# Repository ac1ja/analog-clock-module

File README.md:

# analog-clock-module

This repo contains all the firmware and hardware for the analog-clock-module.

If you're looking for the latest docs/builds, see our [Releases Page](https://github.com/ac1ja/analog-clock-module/releases).

# Getting Started

First, clone this repo (and optionally checkout a branch)

```shell
git clone https://github.com/ac1ja/analog-clock-module.git
cd analog-clock-module
```

# Init Submodules

Some libraries and resources are included as submodules, run the following
command to initialize them before opening the main sch

(If you get a missing library error, make sure to do this)

```shell
git submodule update --init --recursive
```

## Project Layout

If you want to use this project template for yourself, you can find it [here!](https://github.com/KenwoodFox/Project-Template)

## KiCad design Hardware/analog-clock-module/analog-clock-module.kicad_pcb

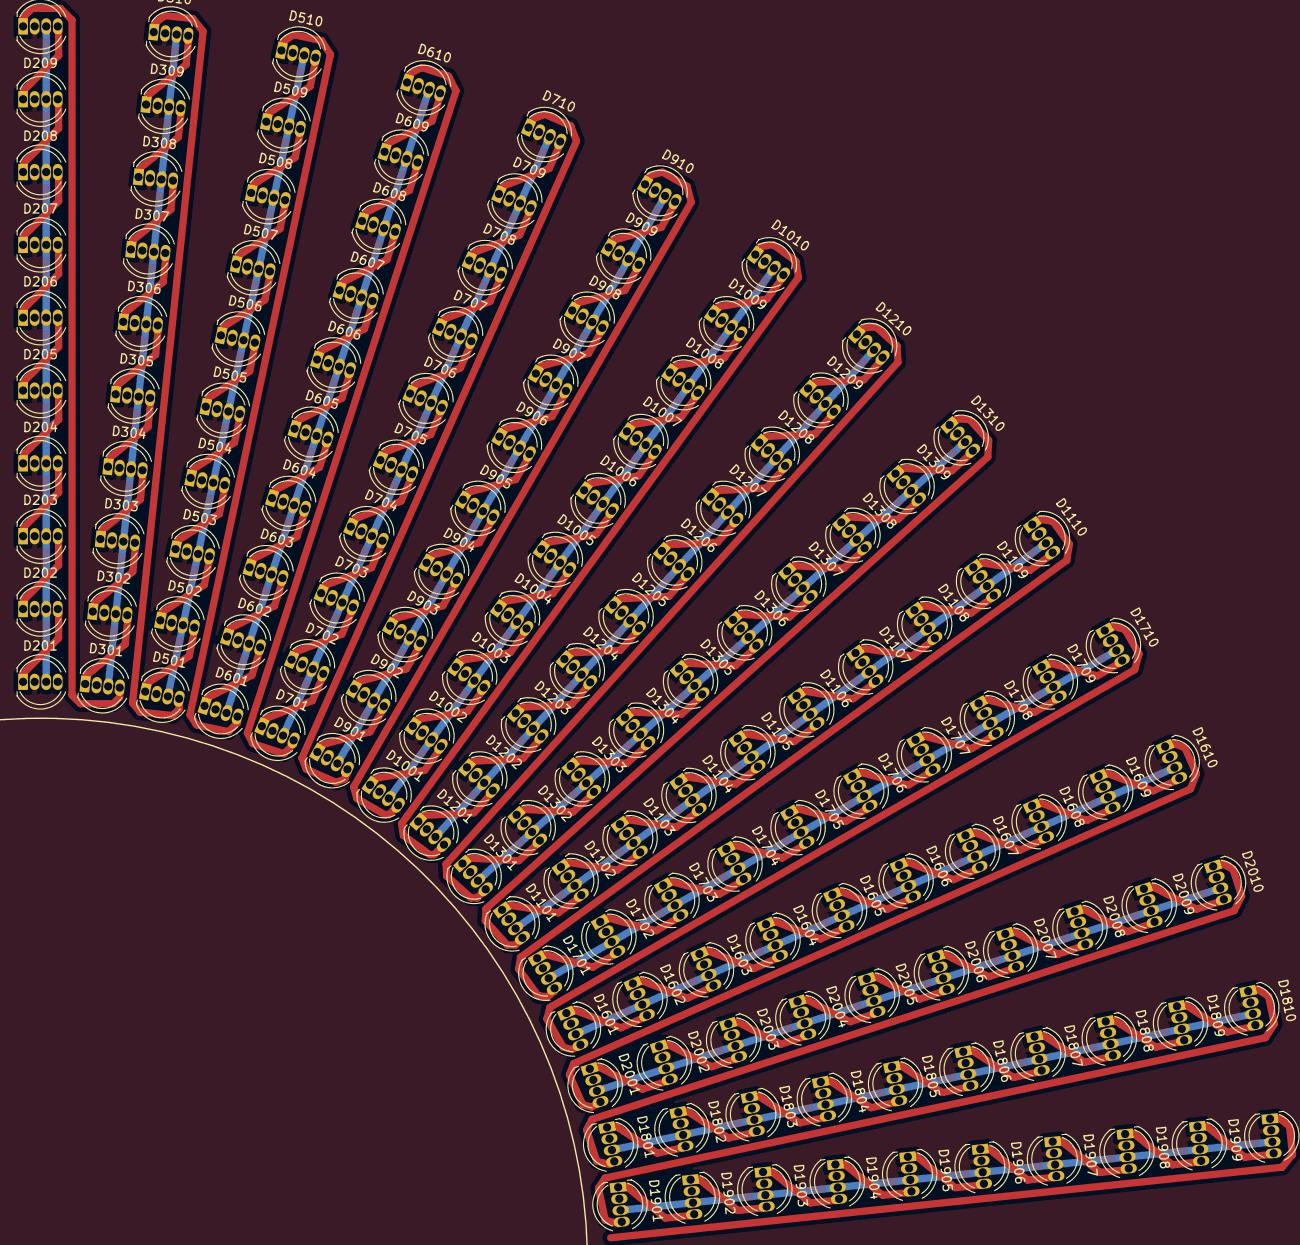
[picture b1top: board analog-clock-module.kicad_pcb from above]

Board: 2 copper layers, 150 parts (0 on the bottom side), 151 nets.

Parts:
D201, D202, D203, D204, D205, D206, D207, D208, D209, D210, D301, D302, D303, D304, D305, D306, D307, D308, D309, D310, D501, D502, D503, D504, D505, D506, D507, D508, D509, D510, D601, D602, D603, D604, D605, D606, D607, D608, D609, D610, D701, D702, D703, D704, D705, D706, D707, D708, D709, D710, D901, D902, D903, D904, D905, D906, D907, D908, D909, D910, D1001, D1002, D1003, D1004, D1005, D1006, D1007, D1008, D1009, D1010, D1101, D1102, D1103, D1104, D1105, D1106, D1107, D1108, D1109, D1110, D1201, D1202, D1203, D1204, D1205, D1206, D1207, D1208, D1209, D1210, D1301, D1302, D1303, D1304, D1305, D1306, D1307, D1308, D1309, D1310, D1601, D1602, D1603, D1604, D1605, D1606, D1607, D1608, D1609, D1610, D1701, D1702, D1703, D1704, D1705, D1706, D1707, D1708, D1709, D1710, D1801, D1802, D1803, D1804, D1805, D1806, D1807, D1808, D1809, D1810, D1901, D1902, D1903, D1904, D1905, D1906, D1907, D1908, D1909, D1910, D2001, D2002, D2003, D2004, D2005, D2006, D2007, D2008, D2009, D2010: NeoPixel_THT; LED_D5.0mm-4_RGB

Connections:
+5V: D201.3 (VDD), D202.3 (VDD), D203.3 (VDD), D204.3 (VDD), D205.3 (VDD), D206.3 (VDD), D207.3 (VDD), D208.3 (VDD), D209.3 (VDD), D210.3 (VDD), D301.3 (VDD), D302.3 (VDD), D303.3 (VDD), D304.3 (VDD), D305.3 (VDD), D306.3 (VDD), D307.3 (VDD), D308.3 (VDD), D309.3 (VDD), D310.3 (VDD), D501.3 (VDD), D502.3 (VDD), D503.3 (VDD), D504.3 (VDD), D505.3 (VDD), D506.3 (VDD), D507.3 (VDD), D508.3 (VDD), D509.3 (VDD), D510.3 (VDD), D601.3 (VDD), D602.3 (VDD), D603.3 (VDD), D604.3 (VDD), D605.3 (VDD), D606.3 (VDD), D607.3 (VDD), D608.3 (VDD), D609.3 (VDD), D610.3 (VDD), D701.3 (VDD), D702.3 (VDD), D703.3 (VDD), D704.3 (VDD), D705.3 (VDD), D706.3 (VDD), D707.3 (VDD), D708.3 (VDD), D709.3 (VDD), D710.3 (VDD), D901.3 (VDD), D902.3 (VDD), D903.3 (VDD), D904.3 (VDD), D905.3 (VDD), D906.3 (VDD), D907.3 (VDD), D908.3 (VDD), D909.3 (VDD), D910.3 (VDD), D1001.3 (VDD), D1002.3 (VDD), D1003.3 (VDD), D1004.3 (VDD), D1005.3 (VDD), D1006.3 (VDD), D1007.3 (VDD), D1008.3 (VDD), D1009.3 (VDD), D1010.3 (VDD), D1101.3 (VDD), D1102.3 (VDD), D1103.3 (VDD), D1104.3 (VDD), D1105.3 (VDD), D1106.3 (VDD), D1107.3 (VDD), D1108.3 (VDD), D1109.3 (VDD), D1110.3 (VDD), D1201.3 (VDD), D1202.3 (VDD), D1203.3 (VDD), D1204.3 (VDD), D1205.3 (VDD), D1206.3 (VDD), D1207.3 (VDD), D1208.3 (VDD), D1209.3 (VDD), D1210.3 (VDD), D1301.3 (VDD), D1302.3 (VDD), D1303.3 (VDD), D1304.3 (VDD), D1305.3 (VDD), D1306.3 (VDD), D1307.3 (VDD), D1308.3 (VDD), D1309.3 (VDD), D1310.3 (VDD), D1601.3 (VDD), D1602.3 (VDD), D1603.3 (VDD), D1604.3 (VDD), D1605.3 (VDD), D1606.3 (VDD), D1607.3 (VDD), D1608.3 (VDD), D1609.3 (VDD), D1610.3 (VDD), D1701.3 (VDD), D1702.3 (VDD), D1703.3 (VDD), D1704.3 (VDD), D1705.3 (VDD), D1706.3 (VDD), D1707.3 (VDD), D1708.3 (VDD), D1709.3 (VDD), D1710.3 (VDD), D1801.3 (VDD), D1802.3 (VDD), D1803.3 (VDD), D1804.3 (VDD), D1805.3 (VDD), D1806.3 (VDD), D1807.3 (VDD), D1808.3 (VDD), D1809.3 (VDD), D1810.3 (VDD), D1901.3 (VDD), D1902.3 (VDD), D1903.3 (VDD), D1904.3 (VDD), D1905.3 (VDD), D1906.3 (VDD), D1907.3 (VDD), D1908.3 (VDD), D1909.3 (VDD), D1910.3 (VDD), D2001.3 (VDD), D2002.3 (VDD), D2003.3 (VDD), D2004.3 (VDD), D2005.3 (VDD), D2006.3 (VDD), D2007.3 (VDD), D2008.3 (VDD), D2009.3 (VDD), D2010.3 (VDD)
/Quadrant/Hour1/Clock Inner Hand1/DOUT: D210.1 (DOUT), D301.4 (DIN)
/Quadrant/Hour1/Clock Inner Hand2/DOUT: D310.1 (DOUT), D501.4 (DIN)
/Quadrant/Hour1/Clock Inner Hand3/DOUT: D510.1 (DOUT), D601.4 (DIN)
/Quadrant/Hour1/Clock Inner Hand4/DOUT: D610.1 (DOUT), D701.4 (DIN)
/Quadrant/Hour1/DOUT: D710.1 (DOUT), D901.4 (DIN)
/Quadrant/Hour2/Clock Inner Hand1/DOUT: D910.1 (DOUT), D1001.4 (DIN)
/Quadrant/Hour2/Clock Inner Hand2/DOUT: D1010.1 (DOUT), D1201.4 (DIN)
/Quadrant/Hour2/Clock Inner Hand3/DOUT: D1210.1 (DOUT), D1301.4 (DIN)
/Quadrant/Hour2/Clock Inner Hand4/DOUT: D1101.4 (DIN), D1310.1 (DOUT)
/Quadrant/Hour2/DOUT: D1110.1 (DOUT), D1701.4 (DIN)
/Quadrant/Hour3/Clock Inner Hand1/DOUT: D1601.4 (DIN), D1710.1 (DOUT)
/Quadrant/Hour3/Clock Inner Hand2/DOUT: D1610.1 (DOUT), D2001.4 (DIN)
/Quadrant/Hour3/Clock Inner Hand3/DOUT: D1801.4 (DIN), D2010.1 (DOUT)
/Quadrant/Hour3/Clock Inner Hand4/DOUT: D1810.1 (DOUT), D1901.4 (DIN)
GND: D201.2 (GND), D202.2 (GND), D203.2 (GND), D204.2 (GND), D205.2 (GND), D206.2 (GND), D207.2 (GND), D208.2 (GND), D209.2 (GND), D210.2 (GND), D301.2 (GND), D302.2 (GND), D303.2 (GND), D304.2 (GND), D305.2 (GND), D306.2 (GND), D307.2 (GND), D308.2 (GND), D309.2 (GND), D310.2 (GND), D501.2 (GND), D502.2 (GND), D503.2 (GND), D504.2 (GND), D505.2 (GND), D506.2 (GND), D507.2 (GND), D508.2 (GND), D509.2 (GND), D510.2 (GND), D601.2 (GND), D602.2 (GND), D603.2 (GND), D604.2 (GND), D605.2 (GND), D606.2 (GND), D607.2 (GND), D608.2 (GND), D609.2 (GND), D610.2 (GND), D701.2 (GND), D702.2 (GND), D703.2 (GND), D704.2 (GND), D705.2 (GND), D706.2 (GND), D707.2 (GND), D708.2 (GND), D709.2 (GND), D710.2 (GND), D901.2 (GND), D902.2 (GND), D903.2 (GND), D904.2 (GND), D905.2 (GND), D906.2 (GND), D907.2 (GND), D908.2 (GND), D909.2 (GND), D910.2 (GND), D1001.2 (GND), D1002.2 (GND), D1003.2 (GND), D1004.2 (GND), D1005.2 (GND), D1006.2 (GND), D1007.2 (GND), D1008.2 (GND), D1009.2 (GND), D1010.2 (GND), D1101.2 (GND), D1102.2 (GND), D1103.2 (GND), D1104.2 (GND), D1105.2 (GND), D1106.2 (GND), D1107.2 (GND), D1108.2 (GND), D1109.2 (GND), D1110.2 (GND), D1201.2 (GND), D1202.2 (GND), D1203.2 (GND), D1204.2 (GND), D1205.2 (GND), D1206.2 (GND), D1207.2 (GND), D1208.2 (GND), D1209.2 (GND), D1210.2 (GND), D1301.2 (GND), D1302.2 (GND), D1303.2 (GND), D1304.2 (GND), D1305.2 (GND), D1306.2 (GND), D1307.2 (GND), D1308.2 (GND), D1309.2 (GND), D1310.2 (GND), D1601.2 (GND), D1602.2 (GND), D1603.2 (GND), D1604.2 (GND), D1605.2 (GND), D1606.2 (GND), D1607.2 (GND), D1608.2 (GND), D1609.2 (GND), D1610.2 (GND), D1701.2 (GND), D1702.2 (GND), D1703.2 (GND), D1704.2 (GND), D1705.2 (GND), D1706.2 (GND), D1707.2 (GND), D1708.2 (GND), D1709.2 (GND), D1710.2 (GND), D1801.2 (GND), D1802.2 (GND), D1803.2 (GND), D1804.2 (GND), D1805.2 (GND), D1806.2 (GND), D1807.2 (GND), D1808.2 (GND), D1809.2 (GND), D1810.2 (GND), D1901.2 (GND), D1902.2 (GND), D1903.2 (GND), D1904.2 (GND), D1905.2 (GND), D1906.2 (GND), D1907.2 (GND), D1908.2 (GND), D1909.2 (GND), D1910.2 (GND), D2001.2 (GND), D2002.2 (GND), D2003.2 (GND), D2004.2 (GND), D2005.2 (GND), D2006.2 (GND), D2007.2 (GND), D2008.2 (GND), D2009.2 (GND), D2010.2 (GND)
unnamed: D201.1 (DOUT), D202.4 (DIN)
unnamed: D202.1 (DOUT), D203.4 (DIN)
unnamed: D203.1 (DOUT), D204.4 (DIN)
unnamed: D204.1 (DOUT), D205.4 (DIN)
unnamed: D205.1 (DOUT), D206.4 (DIN)
unnamed: D206.1 (DOUT), D207.4 (DIN)
unnamed: D207.1 (DOUT), D208.4 (DIN)
unnamed: D208.1 (DOUT), D209.4 (DIN)
unnamed: D209.1 (DOUT), D210.4 (DIN)
unnamed: D301.1 (DOUT), D302.4 (DIN)
unnamed: D302.1 (DOUT), D303.4 (DIN)
unnamed: D303.1 (DOUT), D304.4 (DIN)
unnamed: D304.1 (DOUT), D305.4 (DIN)
unnamed: D305.1 (DOUT), D306.4 (DIN)
unnamed: D306.1 (DOUT), D307.4 (DIN)
unnamed: D307.1 (DOUT), D308.4 (DIN)
unnamed: D308.1 (DOUT), D309.4 (DIN)
unnamed: D309.1 (DOUT), D310.4 (DIN)
unnamed: D501.1 (DOUT), D502.4 (DIN)
unnamed: D502.1 (DOUT), D503.4 (DIN)
unnamed: D503.1 (DOUT), D504.4 (DIN)
unnamed: D504.1 (DOUT), D505.4 (DIN)
unnamed: D505.1 (DOUT), D506.4 (DIN)
unnamed: D506.1 (DOUT), D507.4 (DIN)
unnamed: D507.1 (DOUT), D508.4 (DIN)
unnamed: D508.1 (DOUT), D509.4 (DIN)
unnamed: D509.1 (DOUT), D510.4 (DIN)
unnamed: D601.1 (DOUT), D602.4 (DIN)
unnamed: D602.1 (DOUT), D603.4 (DIN)
unnamed: D603.1 (DOUT), D604.4 (DIN)
unnamed: D604.1 (DOUT), D605.4 (DIN)
unnamed: D605.1 (DOUT), D606.4 (DIN)
unnamed: D606.1 (DOUT), D607.4 (DIN)
unnamed: D607.1 (DOUT), D608.4 (DIN)
unnamed: D608.1 (DOUT), D609.4 (DIN)
unnamed: D609.1 (DOUT), D610.4 (DIN)
unnamed: D701.1 (DOUT), D702.4 (DIN)
unnamed: D702.1 (DOUT), D703.4 (DIN)
unnamed: D703.1 (DOUT), D704.4 (DIN)
unnamed: D704.1 (DOUT), D705.4 (DIN)
unnamed: D705.1 (DOUT), D706.4 (DIN)
unnamed: D706.1 (DOUT), D707.4 (DIN)
unnamed: D707.1 (DOUT), D708.4 (DIN)
unnamed: D708.1 (DOUT), D709.4 (DIN)
unnamed: D709.1 (DOUT), D710.4 (DIN)
unnamed: D901.1 (DOUT), D902.4 (DIN)
unnamed: D902.1 (DOUT), D903.4 (DIN)
unnamed: D903.1 (DOUT), D904.4 (DIN)
unnamed: D904.1 (DOUT), D905.4 (DIN)
unnamed: D905.1 (DOUT), D906.4 (DIN)
unnamed: D906.1 (DOUT), D907.4 (DIN)
unnamed: D907.1 (DOUT), D908.4 (DIN)
unnamed: D908.1 (DOUT), D909.4 (DIN)
unnamed: D909.1 (DOUT), D910.4 (DIN)
unnamed: D1001.1 (DOUT), D1002.4 (DIN)
unnamed: D1002.1 (DOUT), D1003.4 (DIN)
unnamed: D1003.1 (DOUT), D1004.4 (DIN)
unnamed: D1004.1 (DOUT), D1005.4 (DIN)
unnamed: D1005.1 (DOUT), D1006.4 (DIN)
unnamed: D1006.1 (DOUT), D1007.4 (DIN)
unnamed: D1007.1 (DOUT), D1008.4 (DIN)
unnamed: D1008.1 (DOUT), D1009.4 (DIN)
unnamed: D1009.1 (DOUT), D1010.4 (DIN)
unnamed: D1101.1 (DOUT), D1102.4 (DIN)
unnamed: D1102.1 (DOUT), D1103.4 (DIN)
unnamed: D1103.1 (DOUT), D1104.4 (DIN)
unnamed: D1104.1 (DOUT), D1105.4 (DIN)
unnamed: D1105.1 (DOUT), D1106.4 (DIN)
unnamed: D1106.1 (DOUT), D1107.4 (DIN)
unnamed: D1107.1 (DOUT), D1108.4 (DIN)
unnamed: D1108.1 (DOUT), D1109.4 (DIN)
unnamed: D1109.1 (DOUT), D1110.4 (DIN)
unnamed: D1201.1 (DOUT), D1202.4 (DIN)
unnamed: D1202.1 (DOUT), D1203.4 (DIN)
unnamed: D1203.1 (DOUT), D1204.4 (DIN)
unnamed: D1204.1 (DOUT), D1205.4 (DIN)
unnamed: D1205.1 (DOUT), D1206.4 (DIN)
unnamed: D1206.1 (DOUT), D1207.4 (DIN)
unnamed: D1207.1 (DOUT), D1208.4 (DIN)
unnamed: D1208.1 (DOUT), D1209.4 (DIN)
unnamed: D1209.1 (DOUT), D1210.4 (DIN)
unnamed: D1301.1 (DOUT), D1302.4 (DIN)
unnamed: D1302.1 (DOUT), D1303.4 (DIN)
unnamed: D1303.1 (DOUT), D1304.4 (DIN)
unnamed: D1304.1 (DOUT), D1305.4 (DIN)
unnamed: D1305.1 (DOUT), D1306.4 (DIN)
unnamed: D1306.1 (DOUT), D1307.4 (DIN)
unnamed: D1307.1 (DOUT), D1308.4 (DIN)
unnamed: D1308.1 (DOUT), D1309.4 (DIN)
unnamed: D1309.1 (DOUT), D1310.4 (DIN)
unnamed: D1601.1 (DOUT), D1602.4 (DIN)
unnamed: D1602.1 (DOUT), D1603.4 (DIN)
unnamed: D1603.1 (DOUT), D1604.4 (DIN)
unnamed: D1604.1 (DOUT), D1605.4 (DIN)
unnamed: D1605.1 (DOUT), D1606.4 (DIN)
unnamed: D1606.1 (DOUT), D1607.4 (DIN)
unnamed: D1607.1 (DOUT), D1608.4 (DIN)
unnamed: D1608.1 (DOUT), D1609.4 (DIN)
unnamed: D1609.1 (DOUT), D1610.4 (DIN)
unnamed: D1701.1 (DOUT), D1702.4 (DIN)
unnamed: D1702.1 (DOUT), D1703.4 (DIN)
unnamed: D1703.1 (DOUT), D1704.4 (DIN)
unnamed: D1704.1 (DOUT), D1705.4 (DIN)
unnamed: D1705.1 (DOUT), D1706.4 (DIN)
unnamed: D1706.1 (DOUT), D1707.4 (DIN)
unnamed: D1707.1 (DOUT), D1708.4 (DIN)
unnamed: D1708.1 (DOUT), D1709.4 (DIN)
unnamed: D1709.1 (DOUT), D1710.4 (DIN)
unnamed: D1801.1 (DOUT), D1802.4 (DIN)
unnamed: D1802.1 (DOUT), D1803.4 (DIN)
unnamed: D1803.1 (DOUT), D1804.4 (DIN)
unnamed: D1804.1 (DOUT), D1805.4 (DIN)
unnamed: D1805.1 (DOUT), D1806.4 (DIN)
unnamed: D1806.1 (DOUT), D1807.4 (DIN)
unnamed: D1807.1 (DOUT), D1808.4 (DIN)
unnamed: D1808.1 (DOUT), D1809.4 (DIN)
unnamed: D1809.1 (DOUT), D1810.4 (DIN)
unnamed: D1901.1 (DOUT), D1902.4 (DIN)
unnamed: D1902.1 (DOUT), D1903.4 (DIN)
unnamed: D1903.1 (DOUT), D1904.4 (DIN)
unnamed: D1904.1 (DOUT), D1905.4 (DIN)
unnamed: D1905.1 (DOUT), D1906.4 (DIN)
unnamed: D1906.1 (DOUT), D1907.4 (DIN)
unnamed: D1907.1 (DOUT), D1908.4 (DIN)
unnamed: D1908.1 (DOUT), D1909.4 (DIN)
unnamed: D1909.1 (DOUT), D1910.4 (DIN)
unnamed: D2001.1 (DOUT), D2002.4 (DIN)
unnamed: D2002.1 (DOUT), D2003.4 (DIN)
unnamed: D2003.1 (DOUT), D2004.4 (DIN)
unnamed: D2004.1 (DOUT), D2005.4 (DIN)
unnamed: D2005.1 (DOUT), D2006.4 (DIN)
unnamed: D2006.1 (DOUT), D2007.4 (DIN)
unnamed: D2007.1 (DOUT), D2008.4 (DIN)
unnamed: D2008.1 (DOUT), D2009.4 (DIN)
unnamed: D2009.1 (DOUT), D2010.4 (DIN)

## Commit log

2024-05-29 Import from template https://github.com/KenwoodFox/Project-Template
2024-05-29 Fix upstream
2024-05-29 add all components and inital project layout
2024-05-29 bump
2024-06-05 full quadrant
2024-06-05 All done
2024-06-06 Took notes after meeting with nick
2024-06-07 Bump submodules
2024-06-07 bump to k8, inital BOM for nick
2024-06-11 Bump ahead with LED driver
2024-06-11 Clean and move
2024-06-13 Properly bump to k8
2024-06-13 Bump checkout
2024-06-13 Bump after nick meeting
2024-06-13 Bump config for kicad 8
2024-06-13 Add bakeable
2024-07-10 Inital firmware build
2024-07-10 Starts up with all deps
2024-07-10 Add stencil (inital)
2024-07-25 Bump Jig
